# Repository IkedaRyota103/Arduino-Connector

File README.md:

# Arduino-Connector

名前:  
Arduino_UNO_r4_minima互換モジュール  

【注意】Arduinoの導通ピンは3.3V,GND,SDA (A4),SCL(A5)のみです.  
作成者:  
Burglar  
紹介:  
過労死寸前  

回路図:  

PCB:

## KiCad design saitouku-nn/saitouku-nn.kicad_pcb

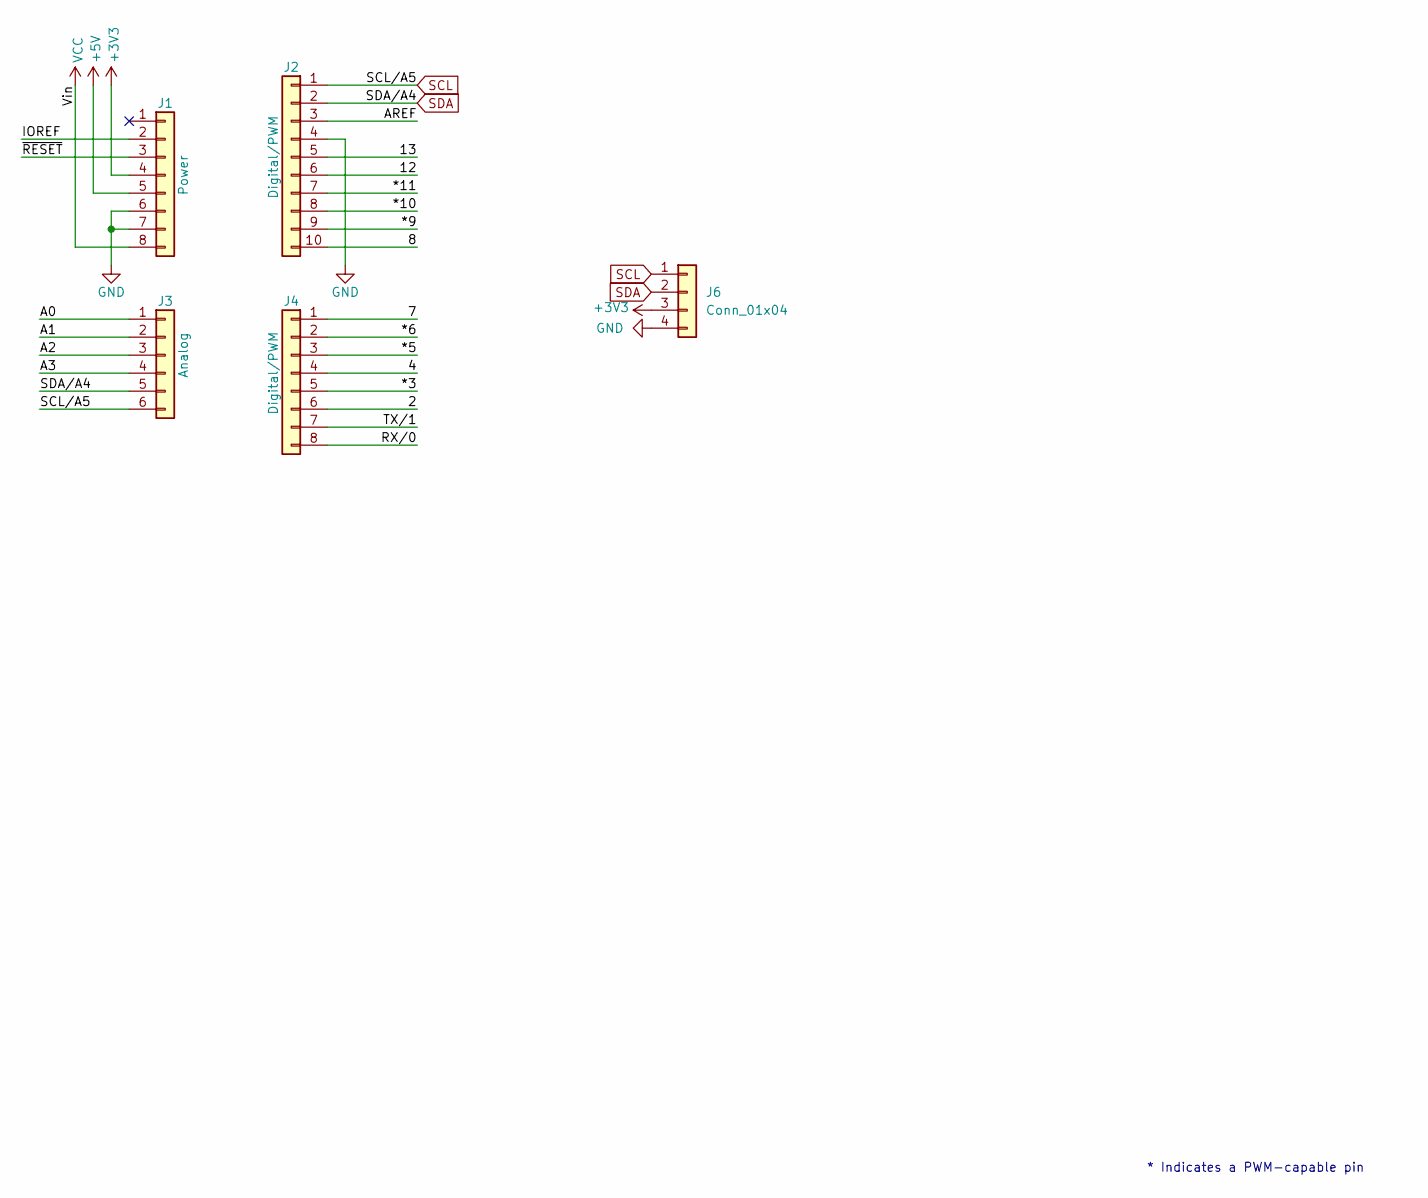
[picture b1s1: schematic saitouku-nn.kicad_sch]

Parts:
J1: Power; PinSocket_1x08_P2.54mm_Vertical
J2: Digital/PWM; PinSocket_1x10_P2.54mm_Vertical
J3: Analog; PinSocket_1x06_P2.54mm_Vertical
J4: Digital/PWM; PinSocket_1x08_P2.54mm_Vertical
J6: Conn_01x04; JST_XA_S04B-XASK-1_1x04_P2.50mm_Horizontal

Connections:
+3V3: J1.4, J6.3
+5V: J1.5
/2: J4.6
/4: J4.4
/7: J4.1
/8: J2.10
/12: J2.6
/13: J2.5
/*3: J4.5
/*5: J4.3
/*6: J4.2
/*9: J2.9
/*10: J2.8
/*11: J2.7
/A0: J3.1
/A1: J3.2
/A2: J3.3
/A3: J3.4
/AREF: J2.3
/IOREF: J1.2
/RX/0: J4.8
/TX/1: J4.7
/~RESET: J1.3
GND: J1.6, J1.7, J2.4, J6.4
SCL: J2.1, J3.6, J6.1
SDA: J2.2, J3.5, J6.2
VCC: J1.8

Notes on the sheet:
* Indicates a PWM-capable pin

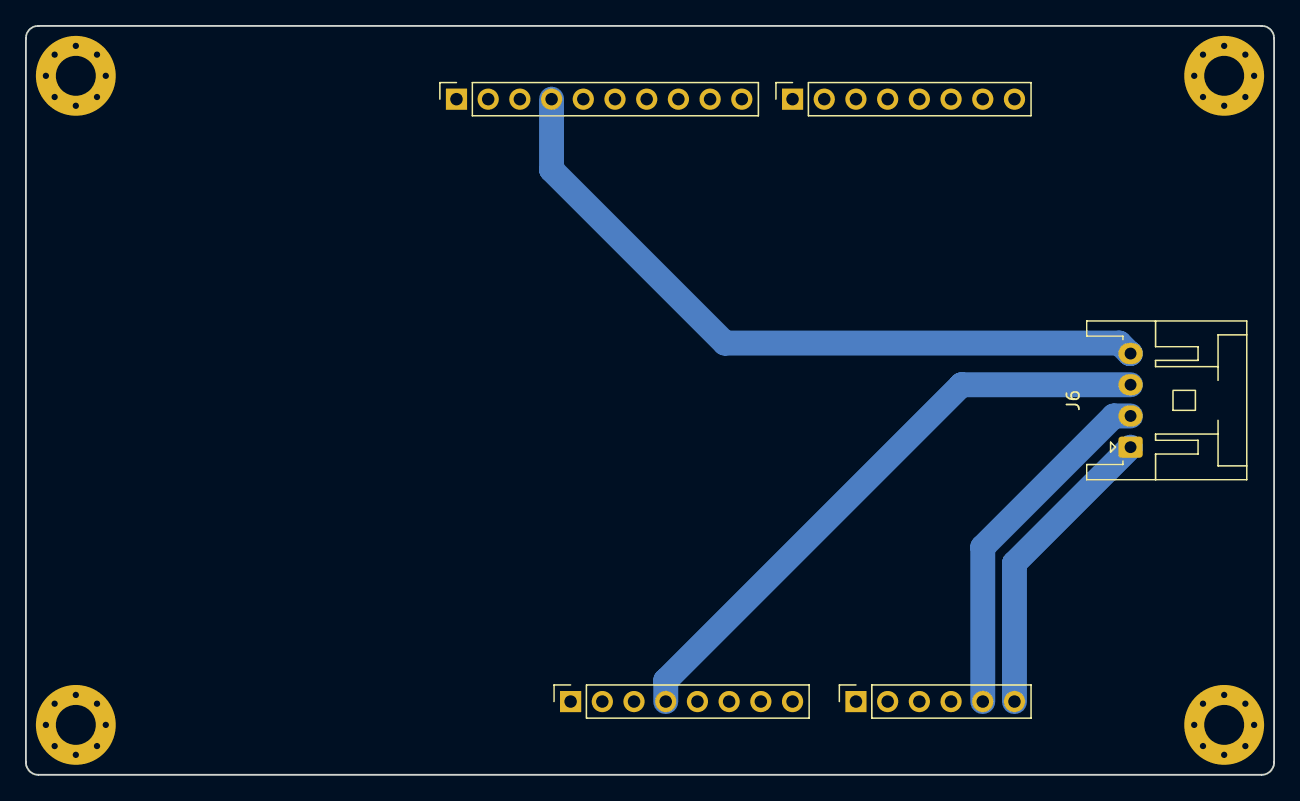
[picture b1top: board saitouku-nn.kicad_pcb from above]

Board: 2 copper layers, 100.0 x 60.0 mm, 5 parts (0 on the bottom side), 4 nets.

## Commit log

2026-05-10 README.md を更新
